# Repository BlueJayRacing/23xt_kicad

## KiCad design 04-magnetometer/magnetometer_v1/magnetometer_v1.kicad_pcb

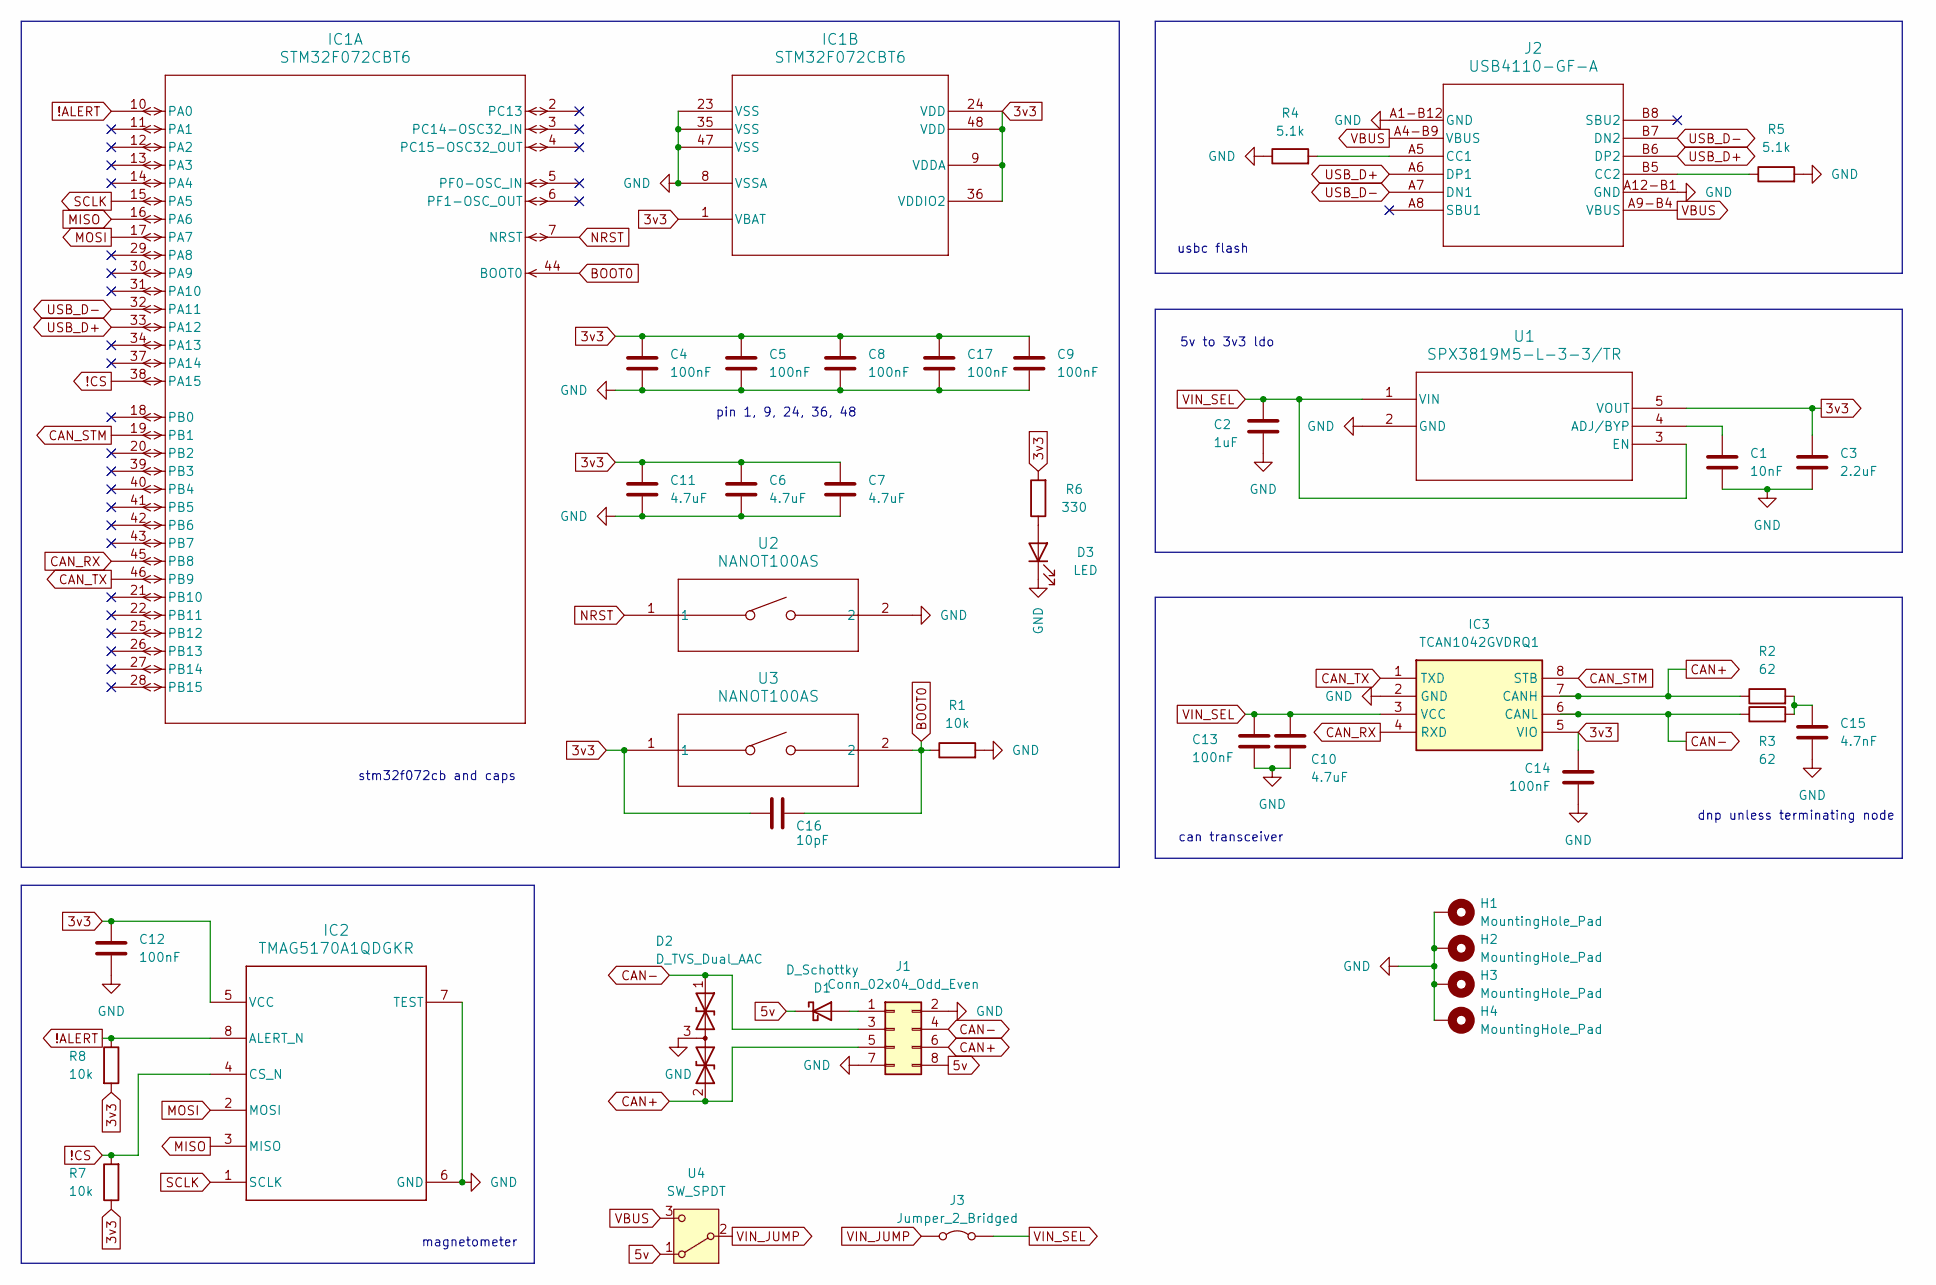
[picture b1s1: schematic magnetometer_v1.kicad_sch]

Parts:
C1: 10nF; C_0402_1005Metric
C2: 1uF; C_0402_1005Metric
C3: 2.2uF; C_0402_1005Metric
C4, C5, C8, C9, C12, C13, C14, C17: 100nF; C_0402_1005Metric
C6, C7, C10, C11: 4.7uF; C_0402_1005Metric
C15: 4.7nF; C_0402_1005Metric
C16: 10pF; C_0402_1005Metric
D1: D_Schottky; D_SOD-323
D2: D_TVS_Dual_AAC; SOT-23-3
D3: LED; LED_0402_1005Metric
H1, H2, H3, H4: MountingHole_Pad; MountingHole_2.2mm_M2_DIN965_Pad
IC1: STM32F072CBT6
IC2: TMAG5170A1QDGKR; TMAG5170A2QDGKR
IC3: TCAN1042GVDRQ1; Mouser Part Number 595-TCAN1042GVDRQ1
J1: Conn_02x04_Odd_Even; PinHeader_2x04_P2.54mm_Vertical
J2: USB4110-GF-A; USB4110-GF-A_GCT
J3: Jumper_2_Bridged; PinHeader_1x02_P2.54mm_Vertical
R1, R7, R8: 10k; R_0402_1005Metric
R2, R3: 62; R_0402_1005Metric
R4, R5: 5.1k; R_0402_1005Metric
R6: 330; R_0402_1005Metric
U1: SPX3819M5-L-3-3/TR; SPX3819M5-L-3-3TR
U2, U3: NANOT100AS; SW_NANOT-AS_CNK
U4: SW_SPDT; SW_JS102011SCQN

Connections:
3v3: C3.1, C4.2, C5.2, C6.2, C7.2, C8.2, C9.2, C11.2, C12.2, C14.2, C16.2, C17.2, IC1.1 (VBAT), IC1.9 (VDDA), IC1.24 (VDD), IC1.36 (VDDIO2), IC1.48 (VDD), IC2.5 (VCC), IC3.5 (VIO), R6.2, R7.1, R8.2, U1.5 (VOUT), U3.1
5v: D1.1 (K), J1.8, U4.1 (A)
!ALERT: IC1.10 (PA0), IC2.8 (ALERT_N), R8.1
!CS: IC1.38 (PA15), IC2.4 (CS_N), R7.2
BOOT0: C16.1, IC1.44 (BOOT0), R1.1, U3.2
CAN+: D2.2 (A2), IC3.7 (CANH), J1.5, J1.6, R2.1
CAN-: D2.1 (A1), IC3.6 (CANL), J1.3, J1.4, R3.1
CAN_RX: IC1.45 (PB8), IC3.4 (RXD)
CAN_STM: IC1.19 (PB1), IC3.8 (STB)
CAN_TX: IC1.46 (PB9), IC3.1 (TXD)
GND: C1.2, C2.2, C3.2, C4.1, C5.1, C6.1, C7.1, C8.1, C9.1, C10.2, C11.1, C12.1, C13.2, C14.1, C15.2, C17.1, D2.3 (common), D3.1 (K), H1.1, H2.1, H3.1, H4.1, IC1.8 (VSSA), IC1.23 (VSS), IC1.35 (VSS), IC1.47 (VSS), IC2.6 (GND), IC2.7 (TEST), IC3.2 (GND), J1.2, J1.7, J2.15, J2.16, J2.17, J2.18, J2.A1-B12 (GND), J2.A12-B1 (GND), R1.2, R4.1, R5.2, U1.2 (GND), U2.2
MISO: IC1.16 (PA6), IC2.3 (MISO)
MOSI: IC1.17 (PA7), IC2.2 (MOSI)
NRST: IC1.7 (NRST), U2.1
unnamed: C15.1, R2.2, R3.2
unnamed: D1.2 (A), J1.1
unnamed: D3.2 (A), R6.1
unnamed: J2.A5 (CC1), R4.2
unnamed: J2.B5 (CC2), R5.1
unnamed: C1.1, U1.4 (ADJ/BYP)
SCLK: IC1.15 (PA5), IC2.1 (SCLK)
USB_D+: IC1.33 (PA12), J2.A6 (DP1), J2.B6 (DP2)
USB_D-: IC1.32 (PA11), J2.A7 (DN1), J2.B7 (DN2)
VBUS: J2.A4-B9 (VBUS), J2.A9-B4 (VBUS), U4.3 (C)
VIN_JUMP: J3.1 (A), U4.2 (B)
VIN_SEL: C2.1, C10.1, C13.1, IC3.3 (VCC), J3.2 (B), U1.1 (VIN), U1.3 (EN)

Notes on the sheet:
dnp unless terminating node
usbc flash
5v to 3v3 ldo
pin 1, 9, 24, 36, 48
can transceiver
magnetometer
stm32f072cb and caps

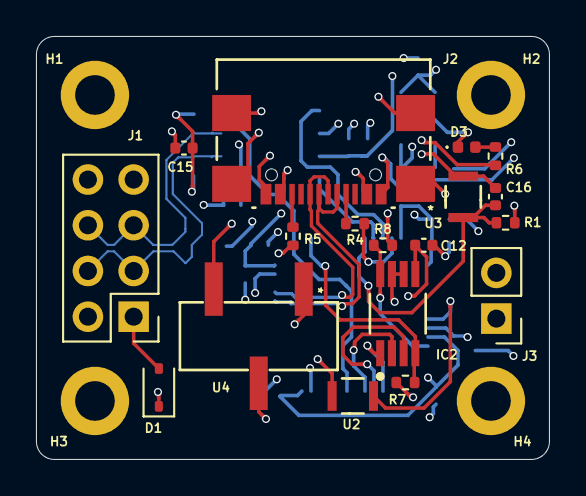
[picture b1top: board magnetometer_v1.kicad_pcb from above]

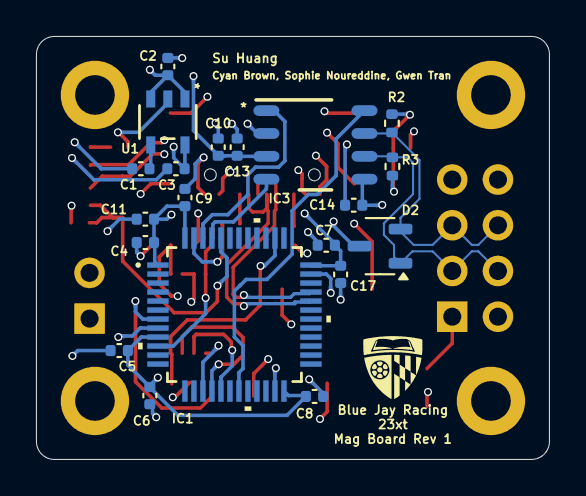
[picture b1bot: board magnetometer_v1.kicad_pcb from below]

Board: 4 copper layers, 28.5 x 23.5 mm, 42 parts (20 on the bottom side), 26 nets.

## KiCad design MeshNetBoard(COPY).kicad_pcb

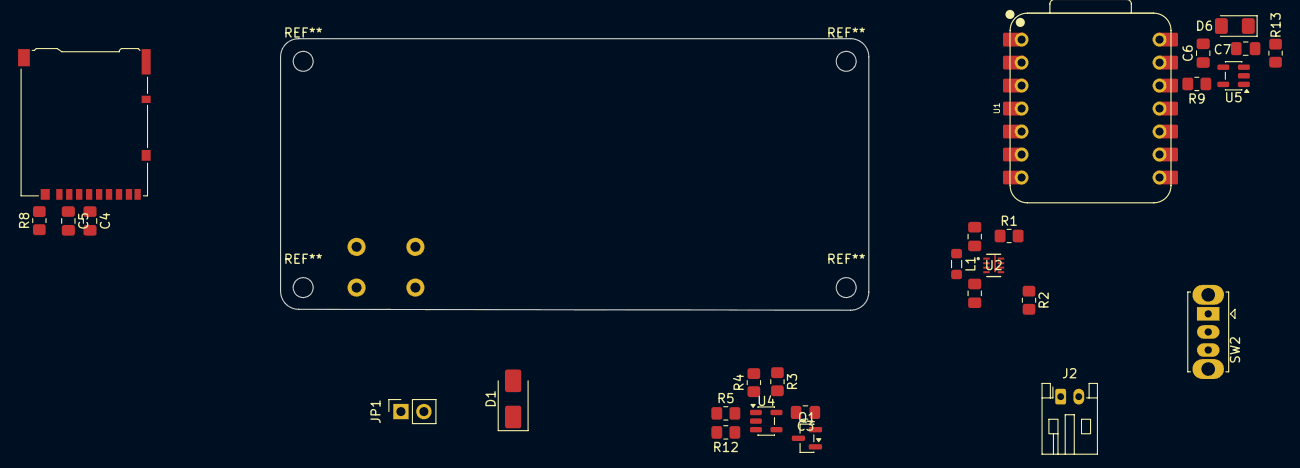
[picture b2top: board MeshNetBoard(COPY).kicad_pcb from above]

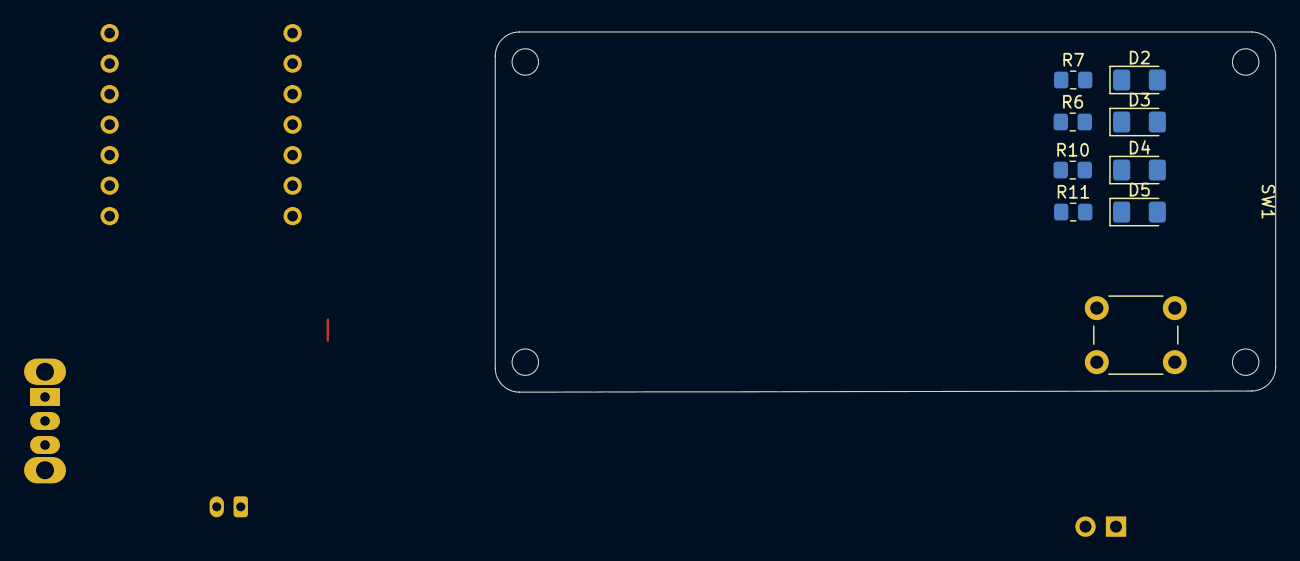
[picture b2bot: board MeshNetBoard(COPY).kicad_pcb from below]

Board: 4 copper layers, 65.0 x 30.0 mm, 37 parts (9 on the bottom side), 31 nets.

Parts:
C1: 47µF; C_0805_2012Metric_Pad1.18x1.45mm_HandSolder
C2: 22µF; C_0805_2012Metric_Pad1.18x1.45mm_HandSolder
C3: 0.1μF; C_0805_2012Metric_Pad1.18x1.45mm_HandSolder
C4: 100nF; C_0805_2012Metric_Pad1.18x1.45mm_HandSolder
C5: 10µF; C_0805_2012Metric_Pad1.18x1.45mm_HandSolder
C6, C7: 4.7µF; C_0805_2012Metric_Pad1.18x1.45mm_HandSolder
D1: SS14; D_SMA
D2, D3, D4, D5, D6: LED; LED_1206_3216Metric_Pad1.42x1.75mm_HandSolder
J2: Conn_01x02; JST_PH_S2B-PH-K_1x02_P2.00mm_Horizontal
J3: Micro_SD_Card_Det_Hirose_DM3AT; microSD_HC_Hirose_DM3AT-SF-PEJM5
JP1: Jumper_2_Open; PinSocket_1x02_P2.54mm_Vertical
L1: 1µH; L_0805_2012Metric_Pad1.05x1.20mm_HandSolder
Q1: Q_PMOS_GSD; SOT-23
R1: 511k; R_0805_2012Metric_Pad1.20x1.40mm_HandSolder
R2: 91k; R_0805_2012Metric_Pad1.20x1.40mm_HandSolder
R3: 1.74M; R_0805_2012Metric_Pad1.20x1.40mm_HandSolder
R4, R12: 1M; R_0805_2012Metric_Pad1.20x1.40mm_HandSolder
R5: 2M; R_0805_2012Metric_Pad1.20x1.40mm_HandSolder
R6, R7, R10, R11: 330; R_0805_2012Metric_Pad1.20x1.40mm_HandSolder
R8: 10k; R_0805_2012Metric_Pad1.20x1.40mm_HandSolder
R9: 2k; R_0805_2012Metric_Pad1.20x1.40mm_HandSolder
R13: 470; R_0805_2012Metric_Pad1.20x1.40mm_HandSolder
SW1: SW_Push; SW_PUSH_6mm_H5mm
SW2: SW_SPST; SW_Slide_SPDT_Straight_CK_OS102011MS2Q
U1: XIAO-ESP32-S3-DIP
U2: TPS631000DRLR; TPS631000DRLR_TEX
U4: MAX9031AU; SOT-23-5
U5: MCP73831-2-OT; SOT-23-5

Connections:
3v3: C4.1, C5.1, D1.1 (K), J3.4 (VDD), R5.1, R8.1, SW1.2, U1.12 (3V3)
5v: C6.1, D6.2 (A), U1.14 (VBUS), U5.4 (V_{DD})
+BATT: C3.2, C7.1, Q1.2 (S), R3.1, SW2.1 (A), U2.5 (EN), U4.5 (V+), U5.3 (V_{BAT})
GND: C1.2, C2.2, C3.1, C4.2, C5.2, C6.2, C7.2, J2.2, J3.6 (VSS), J3.10 (DET_A), J3.SH (SHIELD), R2.2, R4.2, R9.2, R12.2, U1.13 (GND), U2.6 (MODE), U2.7 (GND), U4.2 (V-), U5.2 (V_{SS})
GPIO44: J3.9 (DET_B), U1.8 (GPIO44_D7_RX)
LED1: R7.1, U1.1 (GPIO1_A0_D0)
LED2: R6.1, U1.2 (GPIO2_A1_D1)
LED3: R10.1, U1.3 (GPIO3_A2_D2)
LED4: R11.1, U1.4 (GPIO4_A3_D3)
MISO: J3.7 (DAT0), U1.10 (GPIO8_A9_D9_MISO)
MOSI: J3.3 (CMD), U1.11 (GPIO9_A10_D10_MOSI)
unnamed: D1.2 (A), JP1.1 (A)
unnamed: D2.2 (A), D3.2 (A), D4.2 (A), D5.2 (A), SW1.1
unnamed: D2.1 (K), R7.2
unnamed: D3.1 (K), R6.2
unnamed: D4.1 (K), R10.2
unnamed: D5.1 (K), R11.2
unnamed: D6.1 (K), R13.2
unnamed: J2.1, SW2.2 (B)
unnamed: C1.1, JP1.2 (B), R1.1, U2.1 (VOUT)
unnamed: C2.1, Q1.3 (D), U2.4 (VIN)
unnamed: Q1.1 (G), U4.4
unnamed: R1.2, R2.1, U2.8 (FB)
unnamed: L1.2, U2.3 (LX1)
unnamed: L1.1, U2.2 (LX2)
unnamed: R3.2, R4.1, U4.1 (+)
unnamed: R5.2, R12.1, U4.3 (-)
unnamed: R9.1, U5.5 (PROG)
unnamed: R13.1, U5.1 (STAT)
SCK: J3.5 (CLK), U1.9 (GPIO7_A8_D8_SCK)
SD_DATA: J3.2 (DAT3/CD), R8.2, U1.5 (GPIO5_A4_D4_SDA)
